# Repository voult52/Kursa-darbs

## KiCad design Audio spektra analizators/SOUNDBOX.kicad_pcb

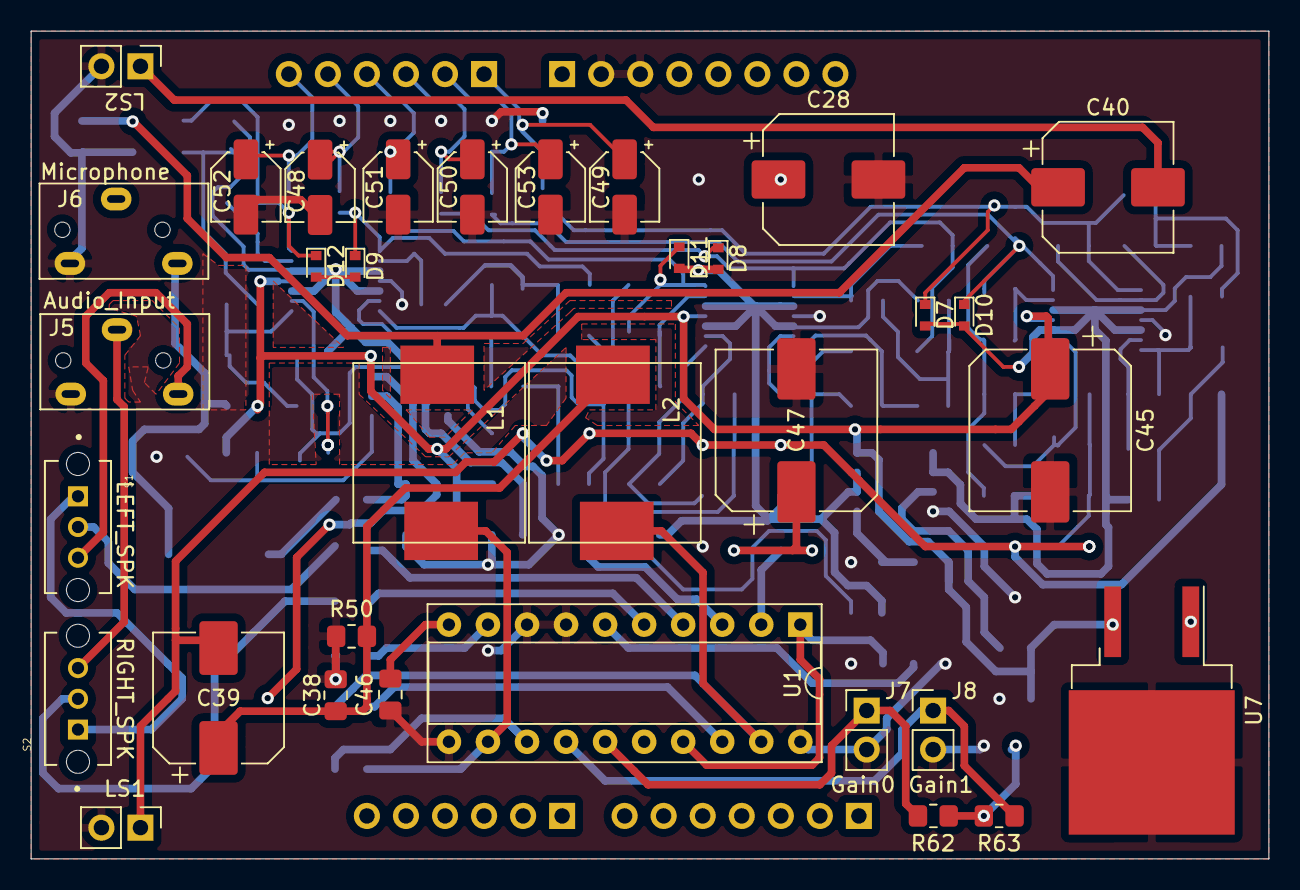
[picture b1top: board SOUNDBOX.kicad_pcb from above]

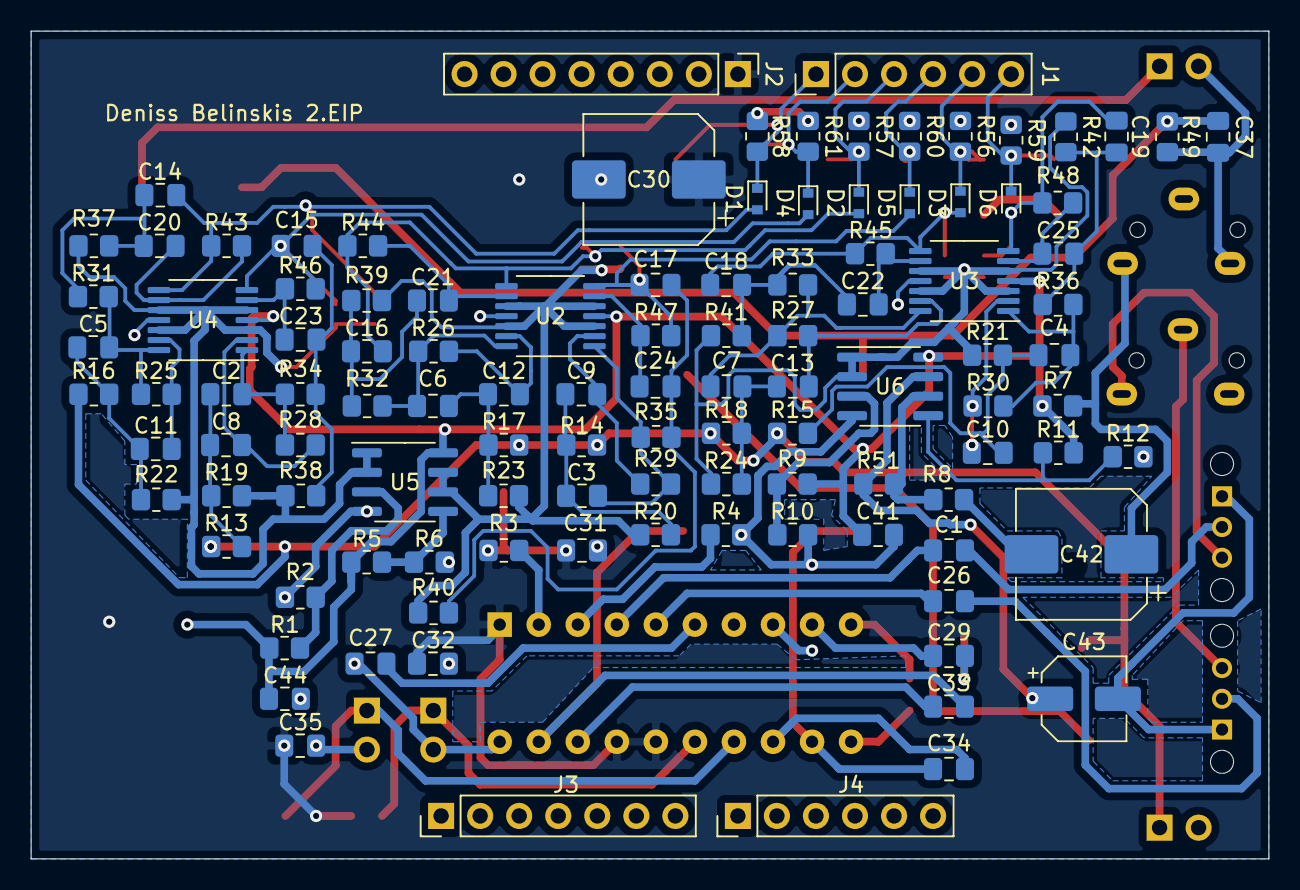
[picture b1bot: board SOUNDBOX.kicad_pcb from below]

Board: 2 copper layers, 80.5 x 53.8 mm, 144 parts (110 on the bottom side), 77 nets.

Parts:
C1, C26, C27, C29: 1000n; C_0805_2012Metric_Pad1.18x1.45mm_HandSolder
C2, C5, C6, C8, C11, C12, C14, C15, C16, C20, C21, C23, C33, C34: 220n; C_0805_2012Metric_Pad1.18x1.45mm_HandSolder
C3, C9, C17, C24: 22n; C_0805_2012Metric_Pad1.18x1.45mm_HandSolder
C4, C10, C19, C25: 1n; C_0805_2012Metric_Pad1.18x1.45mm_HandSolder
C7, C13, C18, C22: 2n2; C_0805_2012Metric_Pad1.18x1.45mm_HandSolder
C28, C30, C39, C40: 470u; CP_Elec_8x10
C31, C32, C35, C41, C44, C46: 100n; C_0805_2012Metric_Pad1.18x1.45mm_HandSolder
C37, C38: 680n; C_0805_2012Metric_Pad1.18x1.45mm_HandSolder
C42: 10u; CP_Elec_8x10
C43: 2u2; CP_Elec_5x3
C45, C47: 100u; CP_Elec_10x10
C48, C49, C50, C51, C52, C53: 10u; CP_Elec_4x4.5
D1, D2, D3, D4, D5, D6, D7, D8, D9, D10, D11, D12: 1N4148; D_SOD-523
J1: Screw_Terminal_01x06; PinHeader_1x06_P2.54mm_Vertical
J2: Supply pins; PinHeader_1x08_P2.54mm_Vertical
J3: Digital pins; PinHeader_1x07_P2.54mm_Vertical
J4: Digital pins; PinHeader_1x06_P2.54mm_Vertical
J5: AudioJack3; SEv
J6: AudioJack2; SEv
J7: Gain0; PinHeader_1x02_P2.54mm_Vertical
J8: Gain1; PinHeader_1x02_P2.54mm_Vertical
L1, L2: 22uH; INDUCTOR
LS1, LS2: 4Ohm; PinHeader_1x02_P2.54mm_Vertical
R1, R2, R5, R6, R9, R10: 2k; R_0805_2012Metric_Pad1.20x1.40mm_HandSolder
R3, R4, R7, R11, R12, R15, R21, R36, R42, R51, R62, R63: 10k; R_0805_2012Metric_Pad1.20x1.40mm_HandSolder
R8, R56, R57, R58, R59, R60, R61: 1k; R_0805_2012Metric_Pad1.20x1.40mm_HandSolder
R13, R19, R34, R38: 4k; R_0805_2012Metric_Pad1.20x1.40mm_HandSolder
R14, R20, R35, R40: 6k; R_0805_2012Metric_Pad1.20x1.40mm_HandSolder
R16, R22, R31, R37: 15k; R_0805_2012Metric_Pad1.20x1.40mm_HandSolder
R17, R23, R32, R39: 1k5; R_0805_2012Metric_Pad1.20x1.40mm_HandSolder
R18, R24, R33, R41: 14k; R_0805_2012Metric_Pad1.20x1.40mm_HandSolder
R25, R43: 30k; R_0805_2012Metric_Pad1.20x1.40mm_HandSolder
R26, R44: 3k; R_0805_2012Metric_Pad1.20x1.40mm_HandSolder
R27, R45: 28k; R_0805_2012Metric_Pad1.20x1.40mm_HandSolder
R28, R46: 8k; R_0805_2012Metric_Pad1.20x1.40mm_HandSolder
R29, R47: 12k; R_0805_2012Metric_Pad1.20x1.40mm_HandSolder
R30: 20k; R_0805_2012Metric_Pad1.20x1.40mm_HandSolder
R48: 20; R_0805_2012Metric_Pad1.20x1.40mm_HandSolder
R49, R50: 4k7; R_0805_2012Metric_Pad1.20x1.40mm_HandSolder
S1, S2: OS102011MS2QN1; SW_OS102011MS2QN1
U1: TPA3122D2(REV1.0); DIP-20_W7.62mm_Socket
U2, U3, U4: LM324; TSSOP-14_4.4x5mm_P0.65mm
U5, U6: LM358; SOIC-8_3.9x4.9mm_P1.27mm
U7: LM7805_TO220; TO-263-2

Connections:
1: C49.1, D1.1, J1.1, R58.2
2: C53.1, D4.1, J1.2, R61.2
3: C50.1, D2.1, J1.3, R57.2
4: C51.1, D5.1, J1.4, R60.2
5: C48.1, D3.1, J1.5, R56.2
6: C52.1, D6.1, J1.6, R59.2
/Sheet5F8DB692/FILTER_IN: C39.2, LS1.1, R13.1, R14.1, R15.1, R16.1, R17.1, R18.1
/Sheet5F8DB692/VCC: C41.2, C44.2, C45.1, R1.2, R5.2, R7.1, R9.2, R11.2, U2.4, U3.4, U4.4, U5.8, U6.8, U7.3
/Sheet5FA98441/Left_in: C1.2, S1.2
/Sheet5FA98441/Right_in: C26.2, S2.2
/Sheet5FA98441/Right_out: C40.2, LS2.1
/Sheet5FA98441/VCC-12: C28.1, C30.1, C31.2, C32.2, C35.2, C46.2, C47.1, J2.1, R3.2, R62.1, R63.1, U1.1, U1.10, U1.16, U1.17, U7.1
/Sheet5FFF3C63/Mic_out: C43.2, S1.1, S2.1
GNDREF: C27.1, C28.2, C29.1, C30.2, C31.1, C32.1, C35.1, C37.2, C38.1, C41.1, C44.1, C45.2, C46.1, C47.2, C48.2, C49.2, C50.2, C51.2, C52.2, C53.2, J2.2, J2.3, J5.S, J6.S, J7.2, J8.2, LS1.2, LS2.2, R2.1, R4.1, R6.1, R10.1, R12.1, R49.1, R50.2, R56.1, R57.1, R58.1, R59.1, R60.1, R61.1, U1.7, U1.8, U1.11, U1.20, U2.11, U3.11, U4.11, U5.4, U6.4, U7.2
unnamed: C1.1, U1.4
unnamed: C2.1, R28.1, R34.1, U4.1
unnamed: C2.2, C8.2, R13.2, R19.1
unnamed: C3.1, R29.2, R35.1, U2.1
unnamed: C3.2, C9.2, R14.2, R20.1
unnamed: C4.1, R30.1, R36.1, U3.1
unnamed: C5.1, R25.2, R31.1, U4.14
unnamed: C6.1, R26.2, R32.1, U2.14
unnamed: C7.1, R27.1, R33.1, U3.14
unnamed: C8.1, R28.2, U4.2
unnamed: C9.1, R29.1, U2.2
unnamed: C10.1, R30.2, U3.2
unnamed: C4.2, C10.2, R15.2, R21.1
unnamed: C11.1, R25.1, U4.13
unnamed: C5.2, C11.2, R16.2, R22.1
unnamed: C12.1, R26.1, U2.13
unnamed: C6.2, C12.2, R17.2, R23.1
unnamed: C13.1, R27.2, U3.13
unnamed: C7.2, C13.2, R18.2, R24.1
unnamed: C14.1, D1.2, D7.1, R43.2, U4.8
unnamed: C14.2, C20.2, R31.2, R37.1
unnamed: C15.1, D4.2, D10.1, R46.1, U4.7
unnamed: C15.2, C23.2, R34.2, R38.2
unnamed: C16.1, D2.2, D8.1, R44.2, U2.8
unnamed: C16.2, C21.2, R32.2, R39.1
unnamed: C17.1, D5.2, D11.1, R47.1, U2.7
unnamed: C17.2, C24.2, R35.2, R40.2
unnamed: C18.1, D3.2, D9.1, R45.1, U3.8
unnamed: C18.2, C22.2, R33.2, R41.1
unnamed: C19.1, D6.2, D12.1, R48.2, U3.7
unnamed: C19.2, C25.2, R36.2, R42.2
unnamed: C20.1, R43.1, U4.9
unnamed: C21.1, R44.1, U2.9
unnamed: C22.1, R45.2, U3.9
unnamed: C23.1, R46.2, U4.6
unnamed: C24.1, R47.2, U2.6
unnamed: C25.1, R48.1, U3.6
unnamed: C26.1, U1.5
unnamed: C27.2, U1.6
unnamed: C29.2, U1.9
unnamed: C33.1, L2.1, U1.19
unnamed: C33.2, U1.18
unnamed: C34.1, L1.2, U1.12
unnamed: C34.2, U1.13
unnamed: C37.1, C40.1, L1.1, R49.2
unnamed: C38.2, C39.1, L2.2, R50.1
unnamed: C42.1, J6.T, R7.2
unnamed: C42.2, R8.2
unnamed: C43.1, R51.2, U6.7
unnamed: D7.2, D10.2, R19.2, R22.2, R37.2, R38.1, U4.3, U4.5, U4.10, U4.12, U5.1, U5.2
unnamed: D8.2, D11.2, R20.2, R23.2, R39.2, R40.1, U2.3, U2.5, U2.10, U2.12, U5.6, U5.7
unnamed: D9.2, D12.2, R21.2, R24.2, R41.2, R42.1, U3.3, U3.5, U3.10, U3.12, U6.1, U6.2
unnamed: J5.R, S2.3
unnamed: J5.T, S1.3
unnamed: J7.1, R62.2, U1.15
unnamed: J8.1, R63.2, U1.14
unnamed: R1.1, R2.2, U5.3
unnamed: R3.1, U1.2
unnamed: R4.2, U1.3
unnamed: R5.1, R6.2, U5.5
unnamed: R9.1, R10.2, U6.3
unnamed: R11.1, R12.2, U6.5
unnamed: R8.1, R51.1, U6.6

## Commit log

2021-01-25 Spektra analizators
